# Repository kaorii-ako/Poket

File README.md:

# Poket

A pocket Bluetooth MP3 player built around an ESP32-S3.

Plays MP3s off a microSD card and sends them either to Bluetooth
headphones (A2DP source) or out a 3.5 mm jack.

> **Rev B changed the MCU.** The board started on an ESP32-S3, which turned out
> to have Bluetooth LE only — no BR/EDR — so A2DP could never have worked on it.
> `soc_caps.h` in ESP-IDF spells it out: the S3 defines `SOC_BLE_SUPPORTED` and
> not `SOC_BT_CLASSIC_SUPPORTED`. The classic ESP32 in the WROOM-32E-R2 has
> both, keeps its 2 MB PSRAM inside the chip package (so GPIO16/17 stay free,
> unlike a WROVER), and costs a USB-UART bridge because it has no native USB. 0.96" OLED, rotary
encoder, three transport buttons, LiPo with USB-C charging and a
coulomb-counting fuel gauge.

| | |
|---|---|
| MCU | ESP32-WROOM-32E-N16R2 (16 MB flash, 2 MB in-package PSRAM) |
| Storage | microSD over SPI |
| DAC | PCM5102A (I2S, internal PLL — no MCLK needed) |
| Headphone amp | PAM8908, charge-pump / ground-centred output |
| Charger | MCP73831, 500 mA, P-FET load share |
| Fuel gauge | BQ27441-G1 with 10 mΩ sense resistor |
| Rail | AP2112K-3.3, separate ferrite-isolated 3V3A for the audio |
| USB | CP2102N-A02 bridge + cross-coupled auto-reset (this part has no native USB) |
| Board | 80 × 54 mm, 4 layer (Sig / solid GND / Sig / Sig) |
| Case | 86 × 60 × 16.8 mm, 3D printed, two shells + slider cap, chamfered edges |

## The board

Top side: ESP32-S3 module and its antenna keepout top-right, audio chain and
power block under where the OLED sits, encoder centre-right, three transport
buttons along the bottom, USB-C bottom-right, 3.5 mm jack top-left.

Bottom side carries the microSD socket and the BOOT/RESET buttons, so the top
face stays clean. Right: all four copper layers together — In1.Cu is a solid
ground plane with no signal on it at all.

Full schematic (also as a PDF: [`docs/poket-schematic.pdf`](docs/poket-schematic.pdf)).
ERC clean — 0 errors, 0 warnings.

## The firmware

ESP-IDF v5.3, C. Reads MP3s off the card with a vendored [minimp3], decodes
into PSRAM and pushes PCM to either sink — I2S to the PCM5102A, or A2DP source
to a paired pair of headphones.

Six themes ship, and they are not palette swaps — a 1-bit 128 x 64 panel has no
colour to vary, so each one earns its difference through layout, typeface,
iconography and motion. Clockwise from top-left: **Minimal**, **Anime**
(a face that blinks on its own timer), **Cassette** (reels that wind across as
the track plays), **Y2K Chrome**, **Brutalist**, **Terminal**. A seventh slot
takes a custom theme uploaded from the browser; that one is *data*, not code,
so an uploaded pack can lay out screens but can never execute on the device.

The two smallest faces are a hand-drawn 5x8 bitmap table
([`tools/font5x8.py`](firmware/tools/font5x8.py)) — rasterising an outline at
7-8 px loses whole stems, and a 1-bit panel has no antialiasing to hide that
with. The rest come from real faces through
[`tools/mkfont.py`](firmware/tools/mkfont.py).

### Build and flash

ESP-IDF v5.3, target `esp32`. Full detail in
[`firmware/README.md`](firmware/README.md).

```bash
. $HOME/esp/esp-idf/export.sh
cd firmware
idf.py set-target esp32          # once
idf.py build
idf.py -p /dev/ttyUSB0 flash monitor
```

`sdkconfig.defaults` carries the flash size, PSRAM, Classic Bluetooth and the
partition table, so a clean tree builds without menuconfig. The CP2102N bridge
handles reset and boot mode, so flashing needs no button presses; if auto-reset
ever fails, hold **BOOT**, tap **RESET**, release **BOOT**.

Then: put MP3s in `/Music` on a FAT32 card, power on, long-press the encoder,
join the `Poket-XXXX` network shown on screen and open **http://192.168.4.1**.

### The web app

Hold the encoder and Poket brings up its own Wi-Fi access point and serves a
page: drag MP3s onto it to write them to the card, browse the library, drive
transport, and pick the screen theme with a **live 128 x 64 preview**. The
preview is not an artist's impression — `web/proto/oled.js` is a port of
`ui/gfx.c` and runs the same theme code against the same generated glyph bytes,
painted at an integer zoom so one panel pixel is exactly N x N screen pixels
with smoothing off.

Four design directions are prototyped in
[`firmware/web/proto/`](firmware/web/proto/) — open `index.html`:

| | |
|---|---|
| `jcard.html` | ink on cassette card stock; upload zone is a blank Side B |
| `bench.html` | desk instrument — keycaps with travel, knurled knob, amber readout |
| `fab.html` | the board documenting itself: silkscreen on solder mask, designators, title block |
| `plain.html` | the canon settings page; the control the other three have to beat |

Wi-Fi and Bluetooth share one radio, so while the page is being served audio
routes out the 3.5 mm jack.

[minimp3]: firmware/components/minimp3/

## Video

| | |
|---|---|
| [`video/poket-promo.mp4`](video/poket-promo.mp4) | 22 s product film — five shots, titles |
| [`video/poket-assembly.mp4`](video/poket-assembly.mp4) | 6.5 s — parts drop in, then a turntable |

Both are rendered from the same Blender scene, which rebuilds from scratch
with `blender/build_scene.py` (set `MODE` to `"promo"` or `"assembly"`).
Encode the PNG sequences with `tools/encode_video.sh`.

## Documentation

- [`docs/BOM.md`](docs/BOM.md) — bill of materials, ~$46/unit
- [`docs/ASSEMBLY.md`](docs/ASSEMBLY.md) — how to build one
- [`docs/DESIGN.md`](docs/DESIGN.md) — why each part was chosen, and the trade-offs
- [`docs/SUBMISSION.md`](docs/SUBMISSION.md) — what's done, what isn't
- [`JOURNAL.md`](JOURNAL.md) — build log

## Repo layout

```
poket.kicad_sch / .kicad_pcb / .kicad_pro   KiCad 10 project
firmware/                                   ESP-IDF app - drivers, audio, UI themes, web app
cad/enclosure.py                            parametric enclosure (FreeCAD, headless)
enclosure/*.step, *.stl                     exported case parts
docs/                                       BOM, assembly, design notes, schematic PDF
fab/                                        gerbers, drill, pick-and-place
images/                                     renders and screenshots
blender/                                    animation scene + board textures
video/                                      promo + assembly animations
tools/                                      fab export, video encode, PCB helper scripts
JOURNAL.md                                  build log
```

## Building the enclosure model

```
flatpak run --filesystem=host --command=FreeCADCmd org.freecad.FreeCAD cad/enclosure.py
```

Everything is driven by the constants at the top of `cad/enclosure.py`, so
if the PCB outline or a connector moves, change the number and re-run.

## Print settings

PETG or PLA, 0.2 mm layers, 4 perimeters, 20 % infill, no supports needed.
Front shell prints face-down, back shell prints tray-up. 4 × M2 heat-set
inserts (3.2 mm OD) in the front shell bosses; 4 × M2 × 12 screws from the
back.

## Status

**Hardware** — ERC **0 errors, 0 warnings**; DRC **0 errors, 0 schematic-parity
issues**, every signal net routed. The enclosure booleans against the real board
STEP with **0.0000 mm³** interference. Gerbers, drill and pick-and-place in
`fab/` are generated from this revision.

**Firmware** — complete and building. ESP-IDF v5.3, `idf.py build` succeeds from
a clean tree; `poket.bin` is 1.5 MB with 64 % of the app partition free. Drivers,
the audio path with A2DP linking, microSD over SPI, the library scanner, `.m3u`
playlists, the 1-bit graphics layer with six themes, the Wi-Fi access point, the
HTTP server and the web app are all in `firmware/`. Build and flash instructions:
[`firmware/README.md`](firmware/README.md).

**Not built.** No board has been fabricated, no part soldered, and no firmware
has ever run on hardware. Every image here is a render. The design is verified
in software and the firmware compiles — but "passes DRC and builds" and "works"
are different claims, and only the first is being made. Full gap list:
[`docs/SUBMISSION.md`](docs/SUBMISSION.md).

Three ground-pour fragments are untied, two of which carry a bypass capacitor's
ground. Documented rather than hidden.

## Design review

> **Not yet reviewed by another person.** This needs a second pair of eyes
> before fabrication, and nobody has given it one yet.
>
> When someone does, record it here: who reviewed it, when, what they flagged,
> and what changed as a result. An unreviewed board is a board with exactly one
> person's blind spots in it — and this project has already had one part choice
> that a reviewer would very likely have caught (the ESP32-S3 cannot do A2DP,
> which is the whole point of the device).

Worth a reviewer's attention in particular:

- **Power** — the MCP73831 charger, the DMG2301L load-share P-FET and the
  AP2112K rail, especially behaviour when USB and battery are both present.
- **The CP2102N block** — the 22.1 k/47.5 k VBUS sense divider and the
  cross-coupled auto-reset pair (`Q2` drives EN, `Q3` drives IO0, emitters
  cross). Both came from datasheets rather than from a copied schematic.
- **Strapping pins** — GPIO0, 2, 12 and 15. GPIO12 is deliberately left
  unconnected and the microSD runs on SPI to keep off it.
- **The antenna keepout** and whether the module is close enough to the board
  edge to radiate properly.

## License

MIT for code, CERN-OHL-S v2 for the hardware design files. See [`LICENSE`](LICENSE).

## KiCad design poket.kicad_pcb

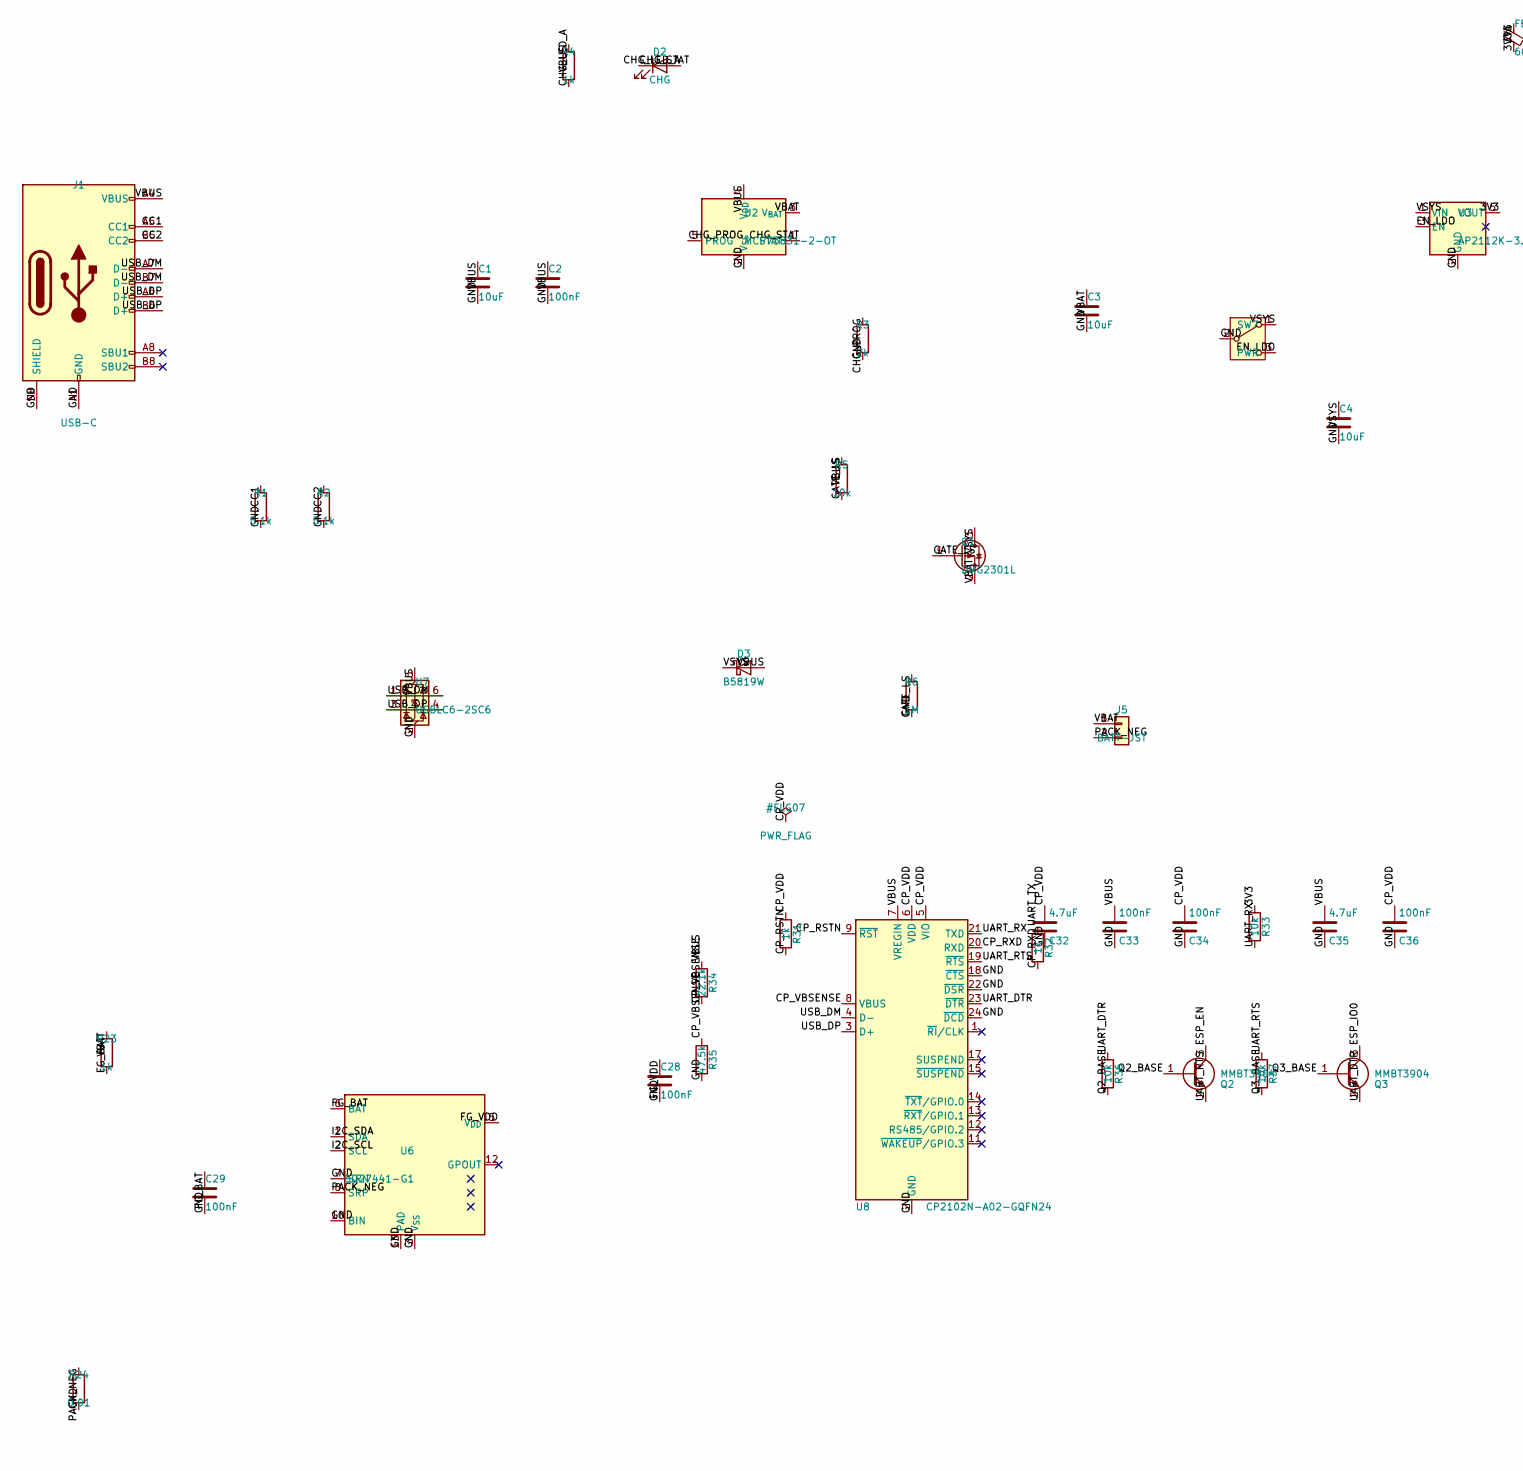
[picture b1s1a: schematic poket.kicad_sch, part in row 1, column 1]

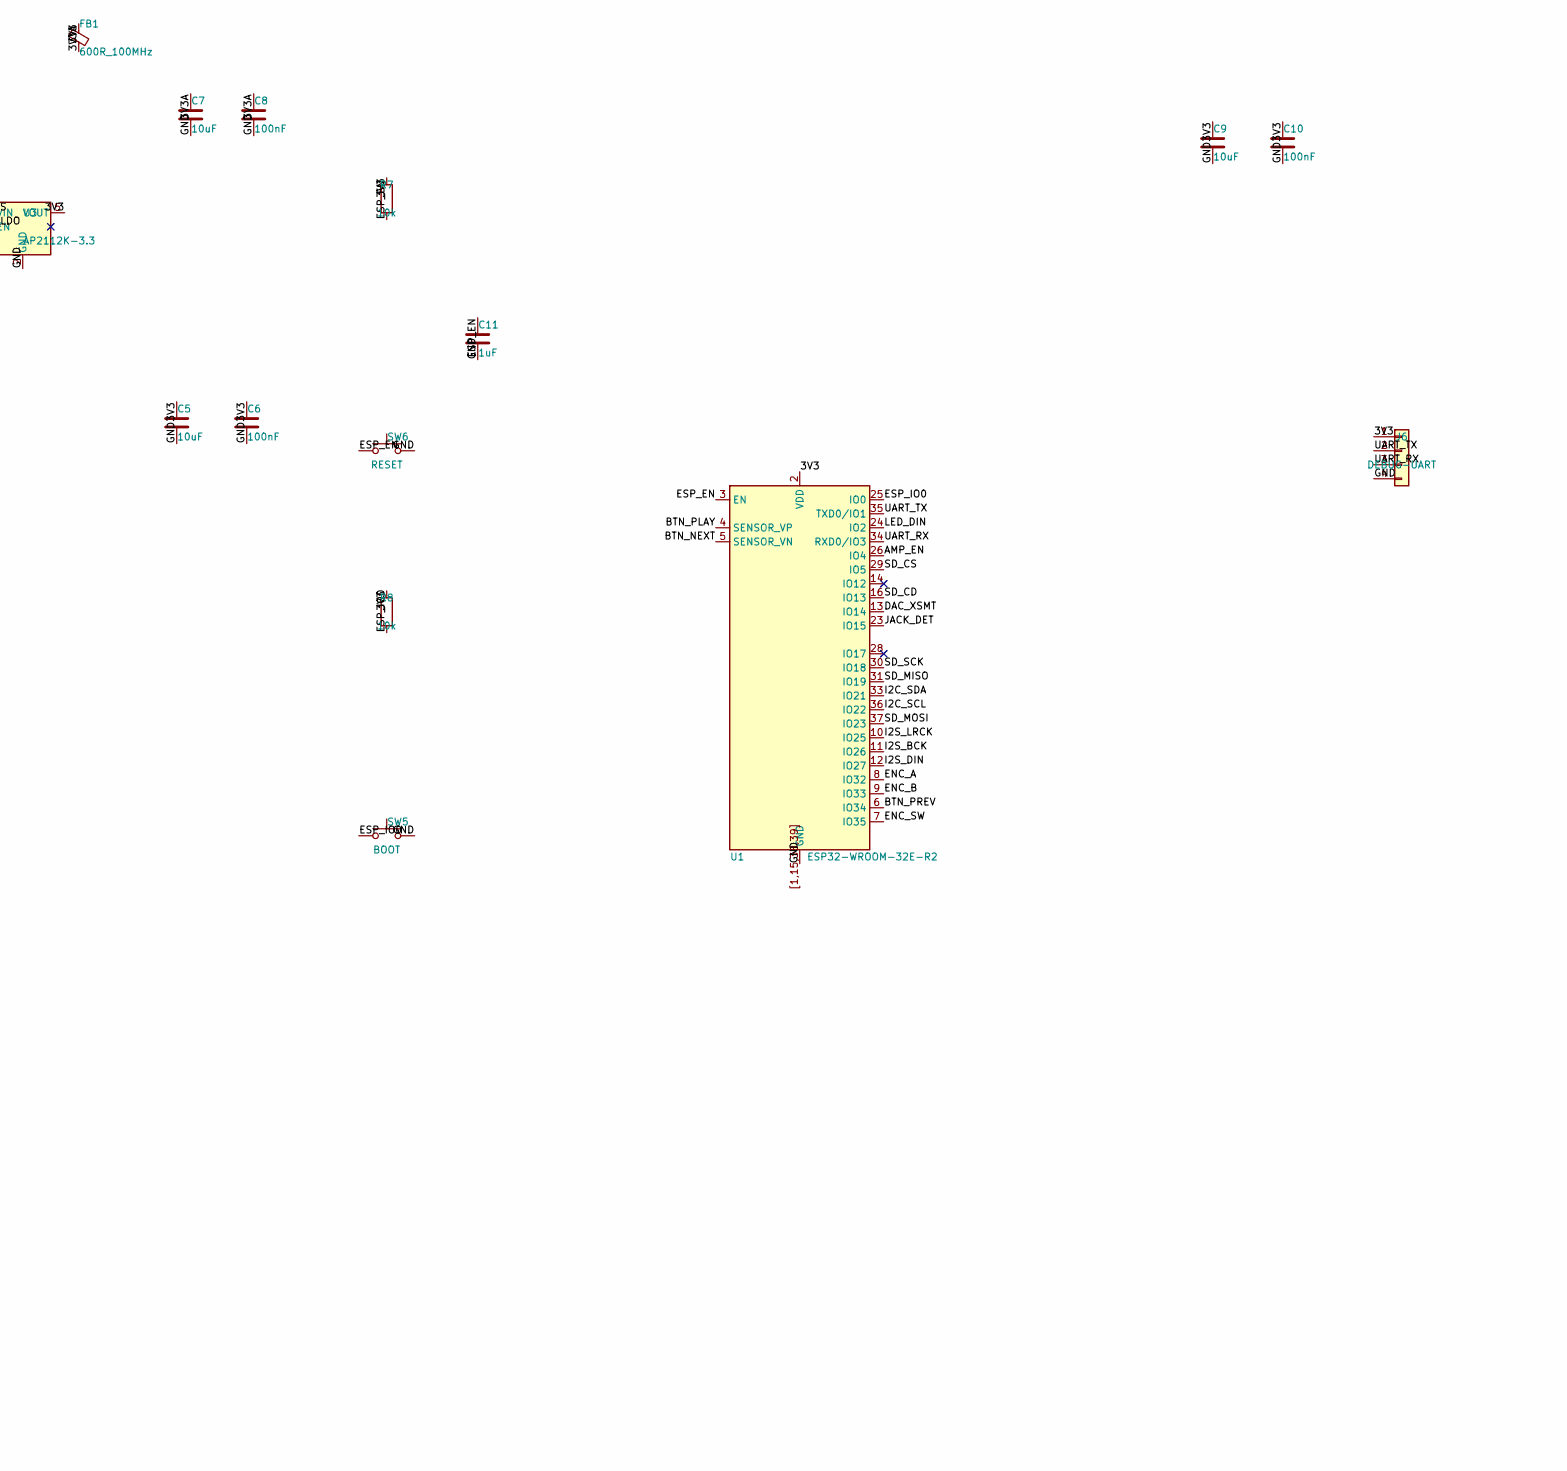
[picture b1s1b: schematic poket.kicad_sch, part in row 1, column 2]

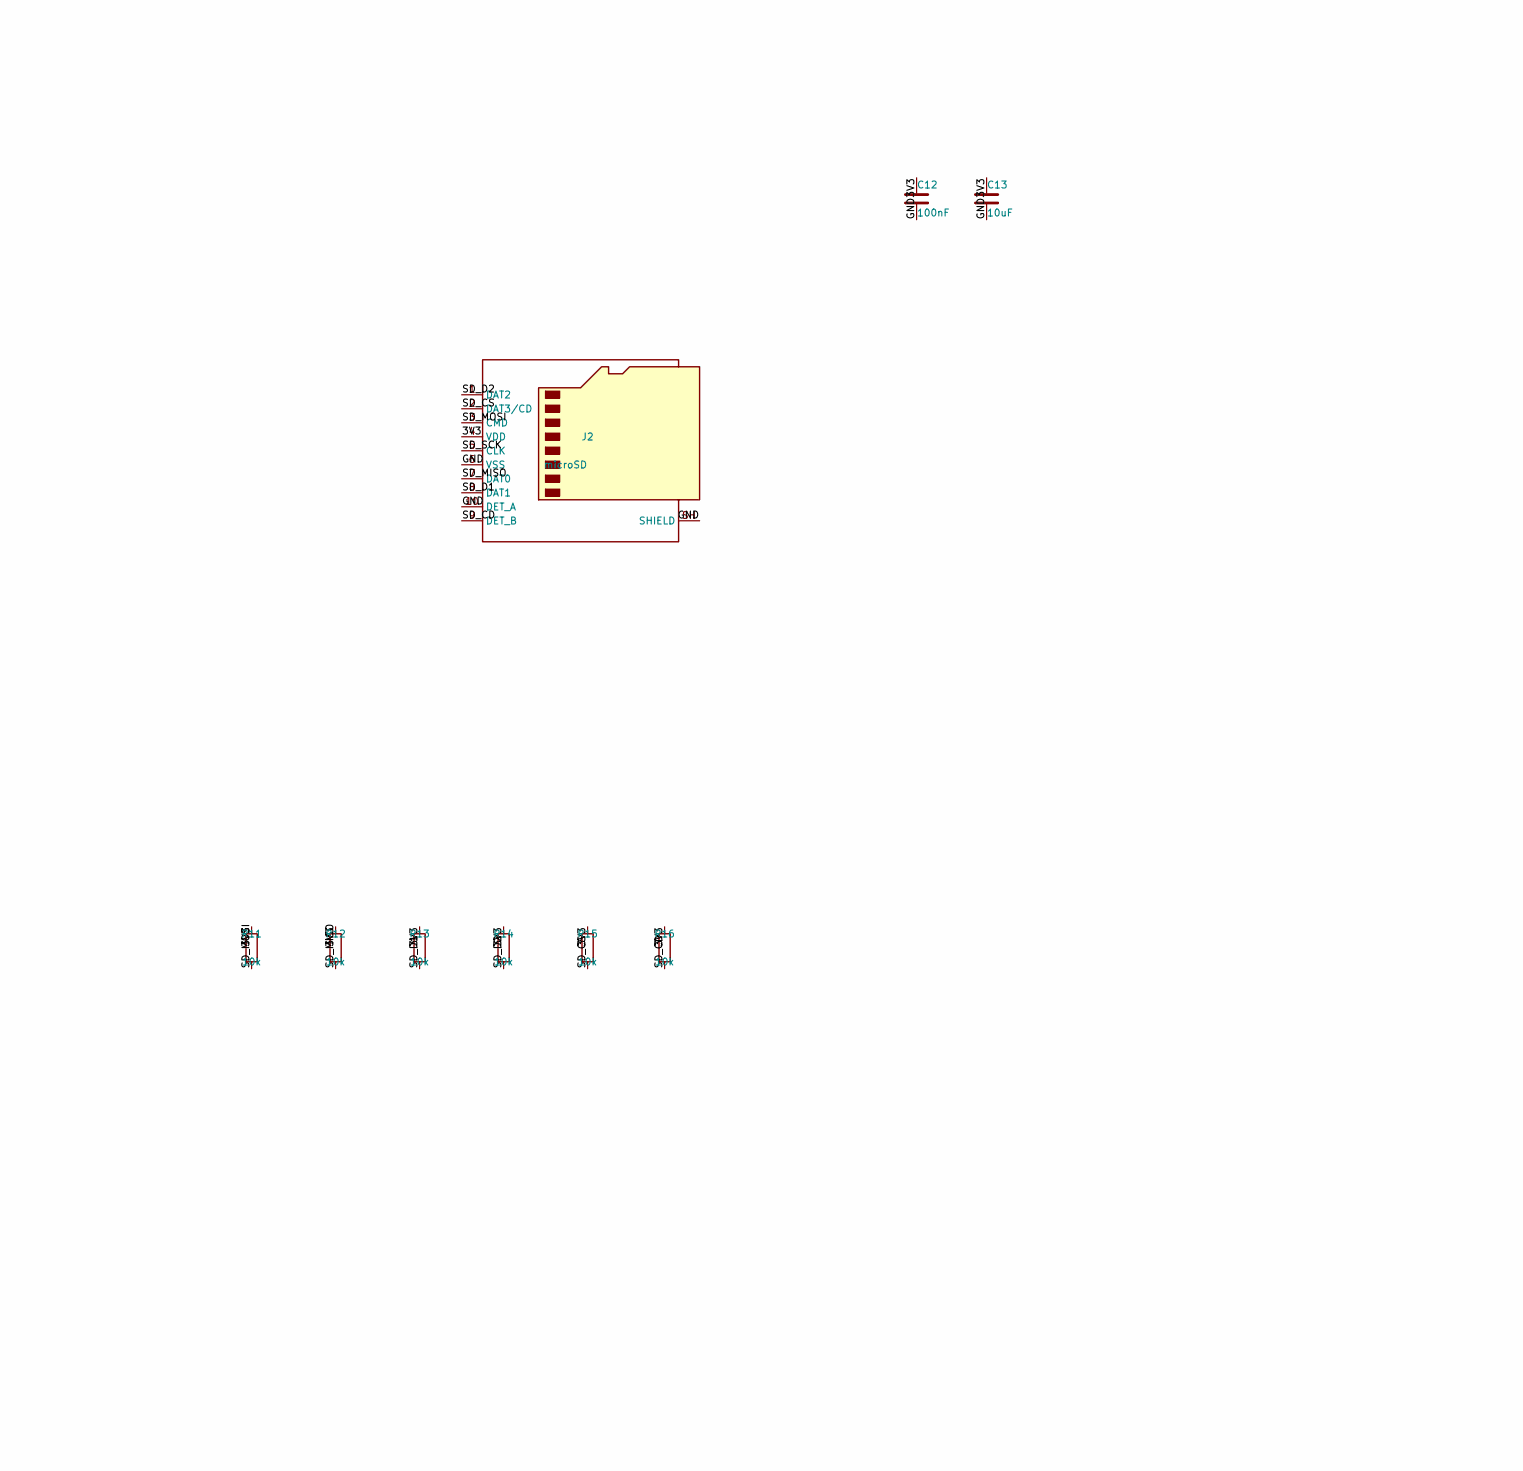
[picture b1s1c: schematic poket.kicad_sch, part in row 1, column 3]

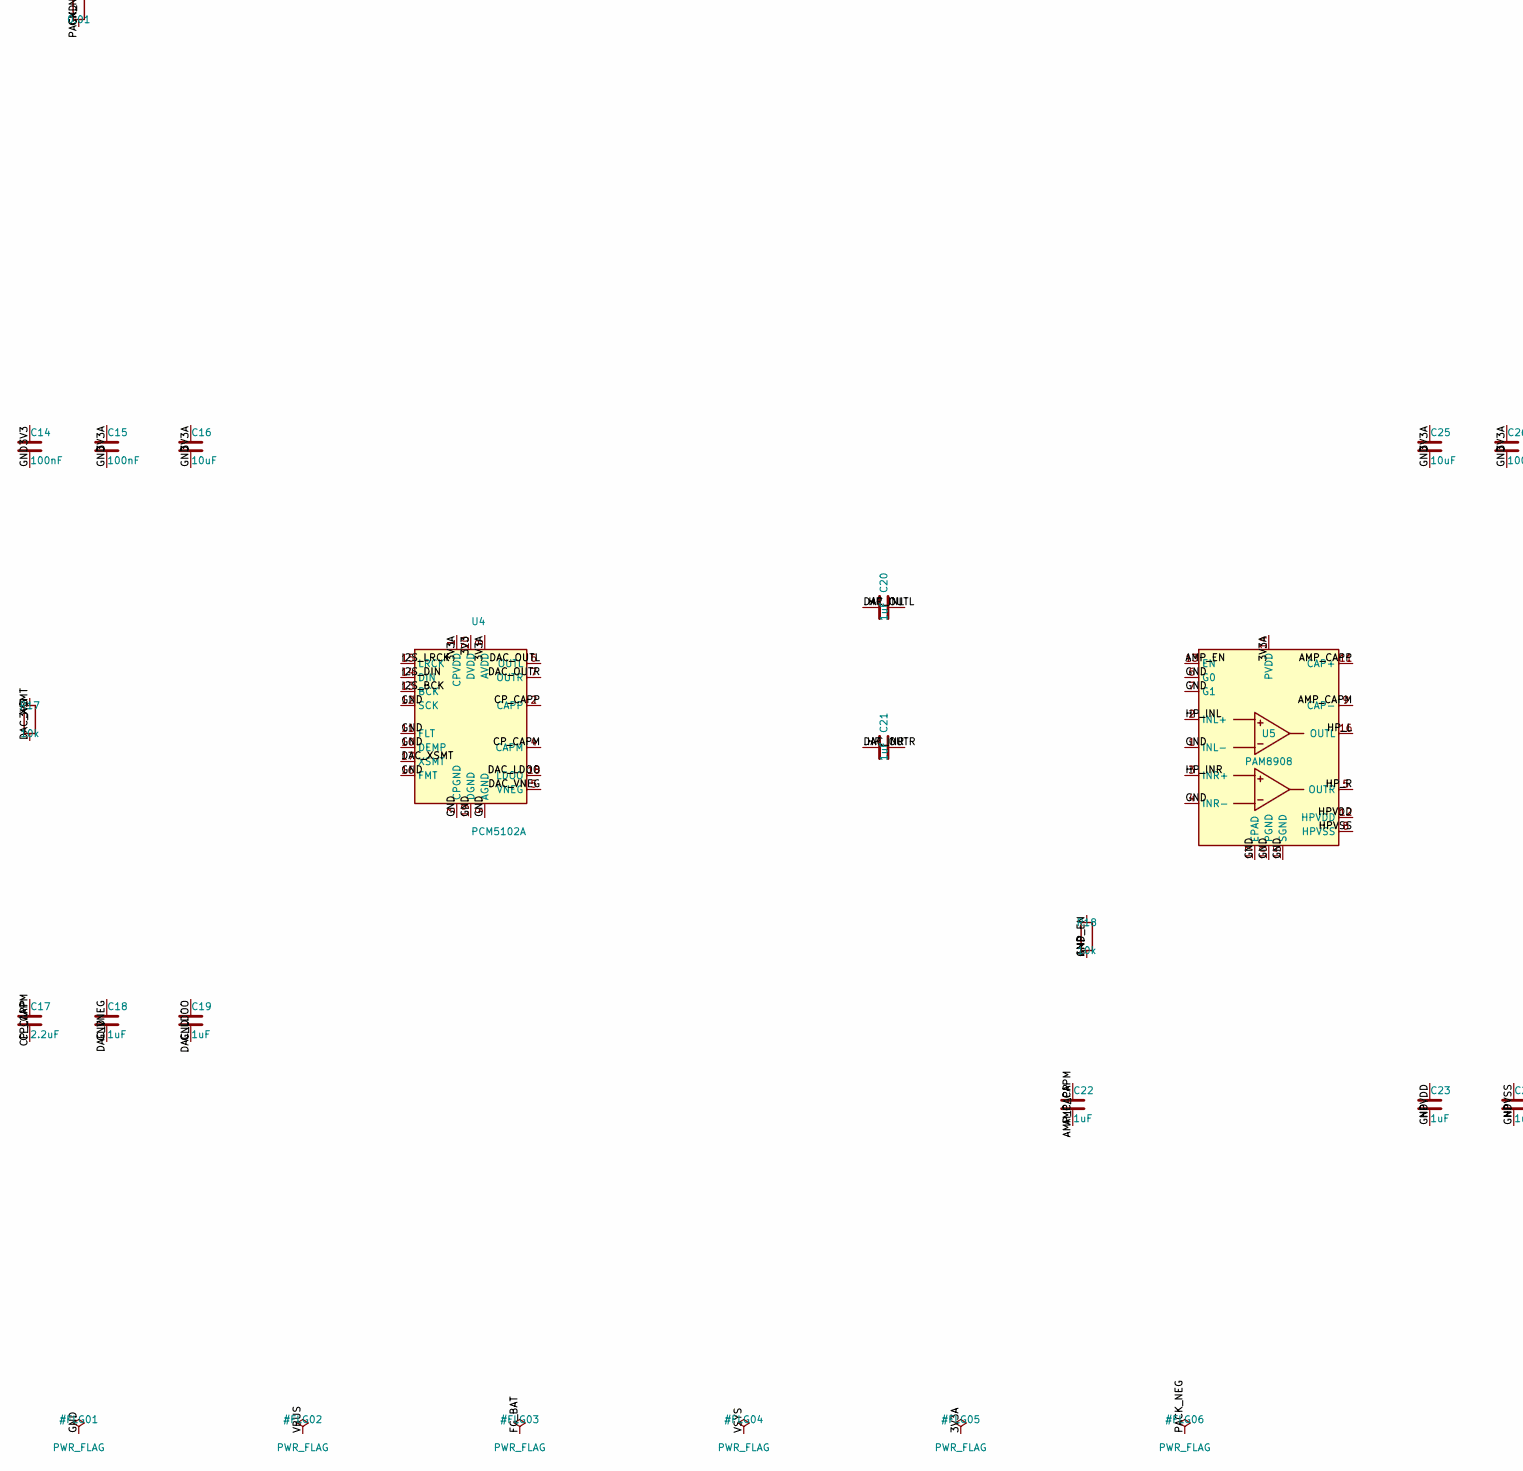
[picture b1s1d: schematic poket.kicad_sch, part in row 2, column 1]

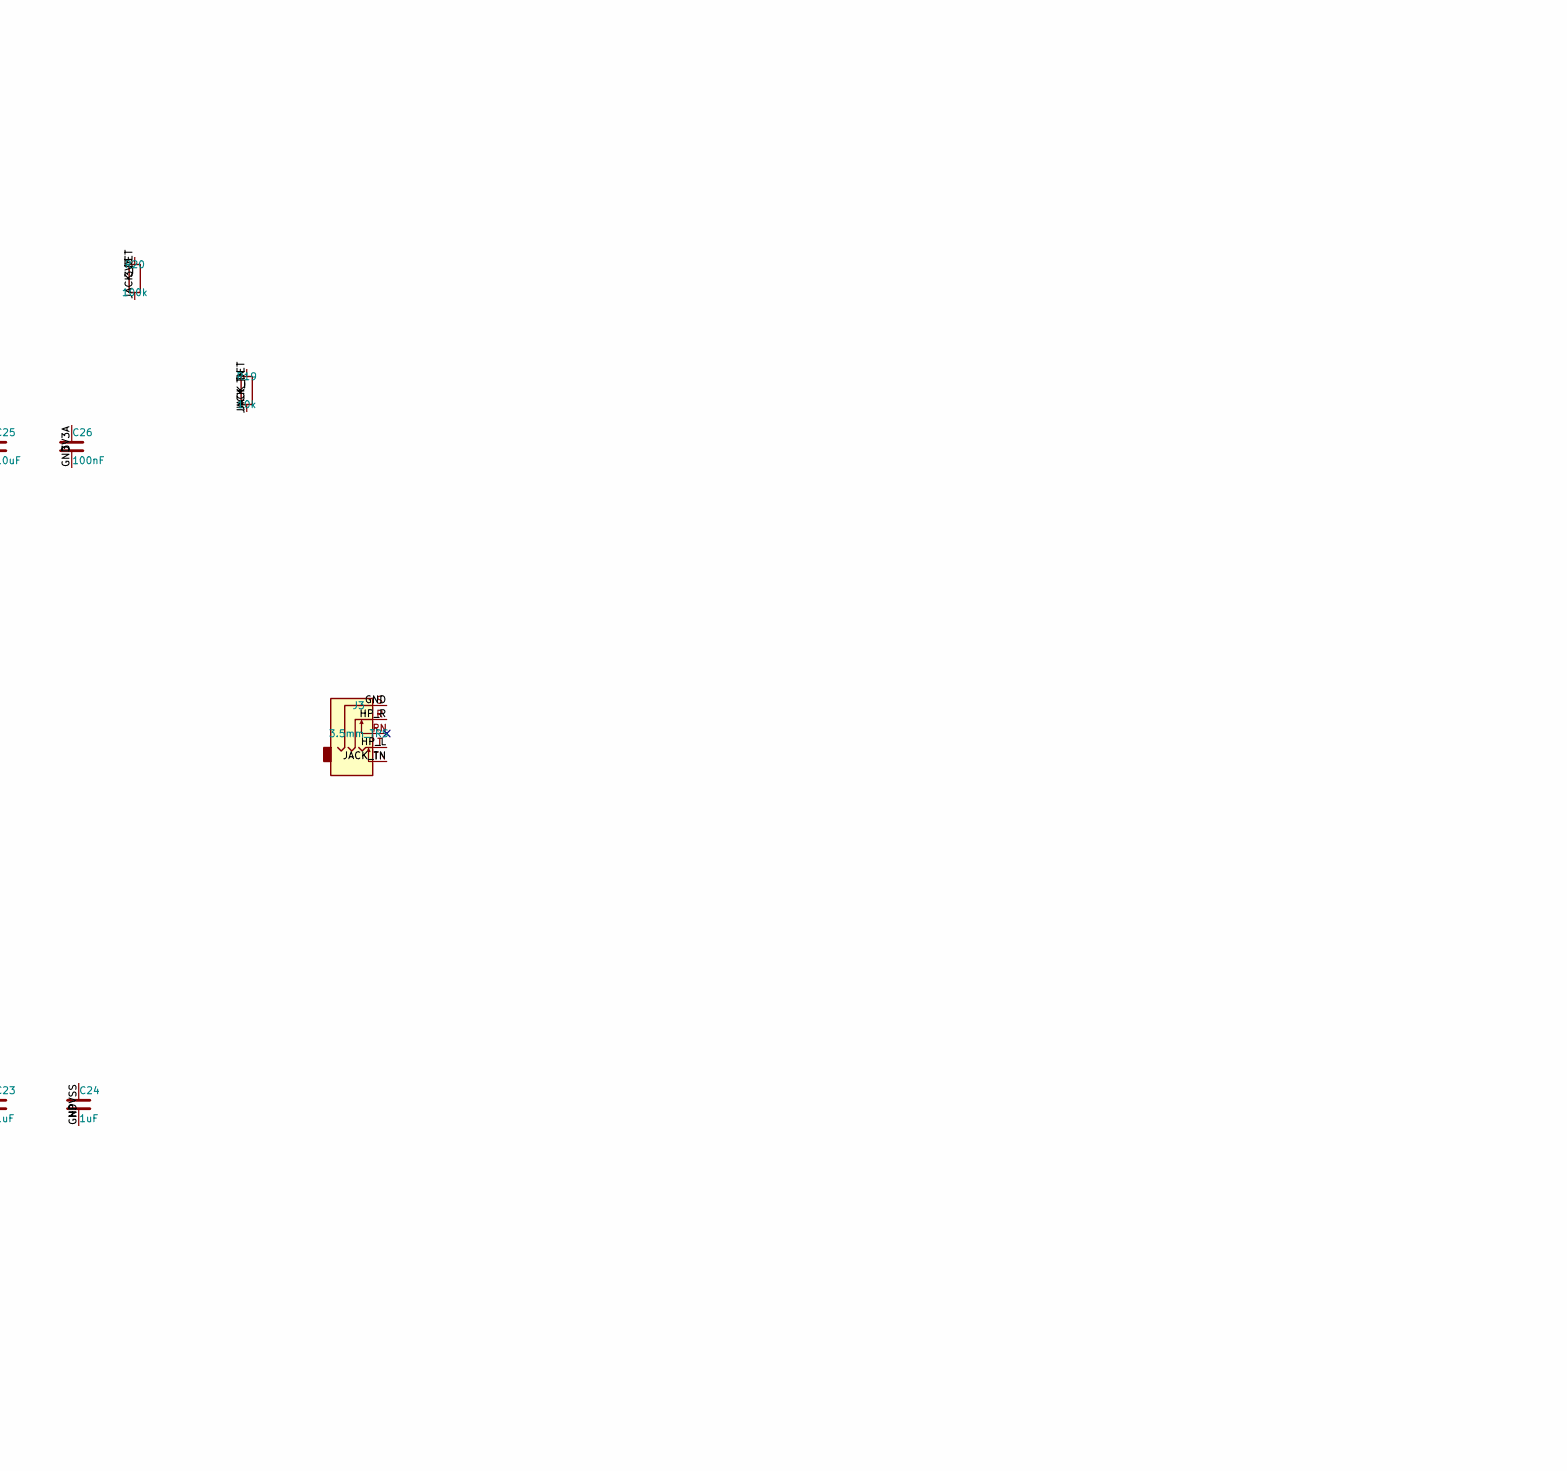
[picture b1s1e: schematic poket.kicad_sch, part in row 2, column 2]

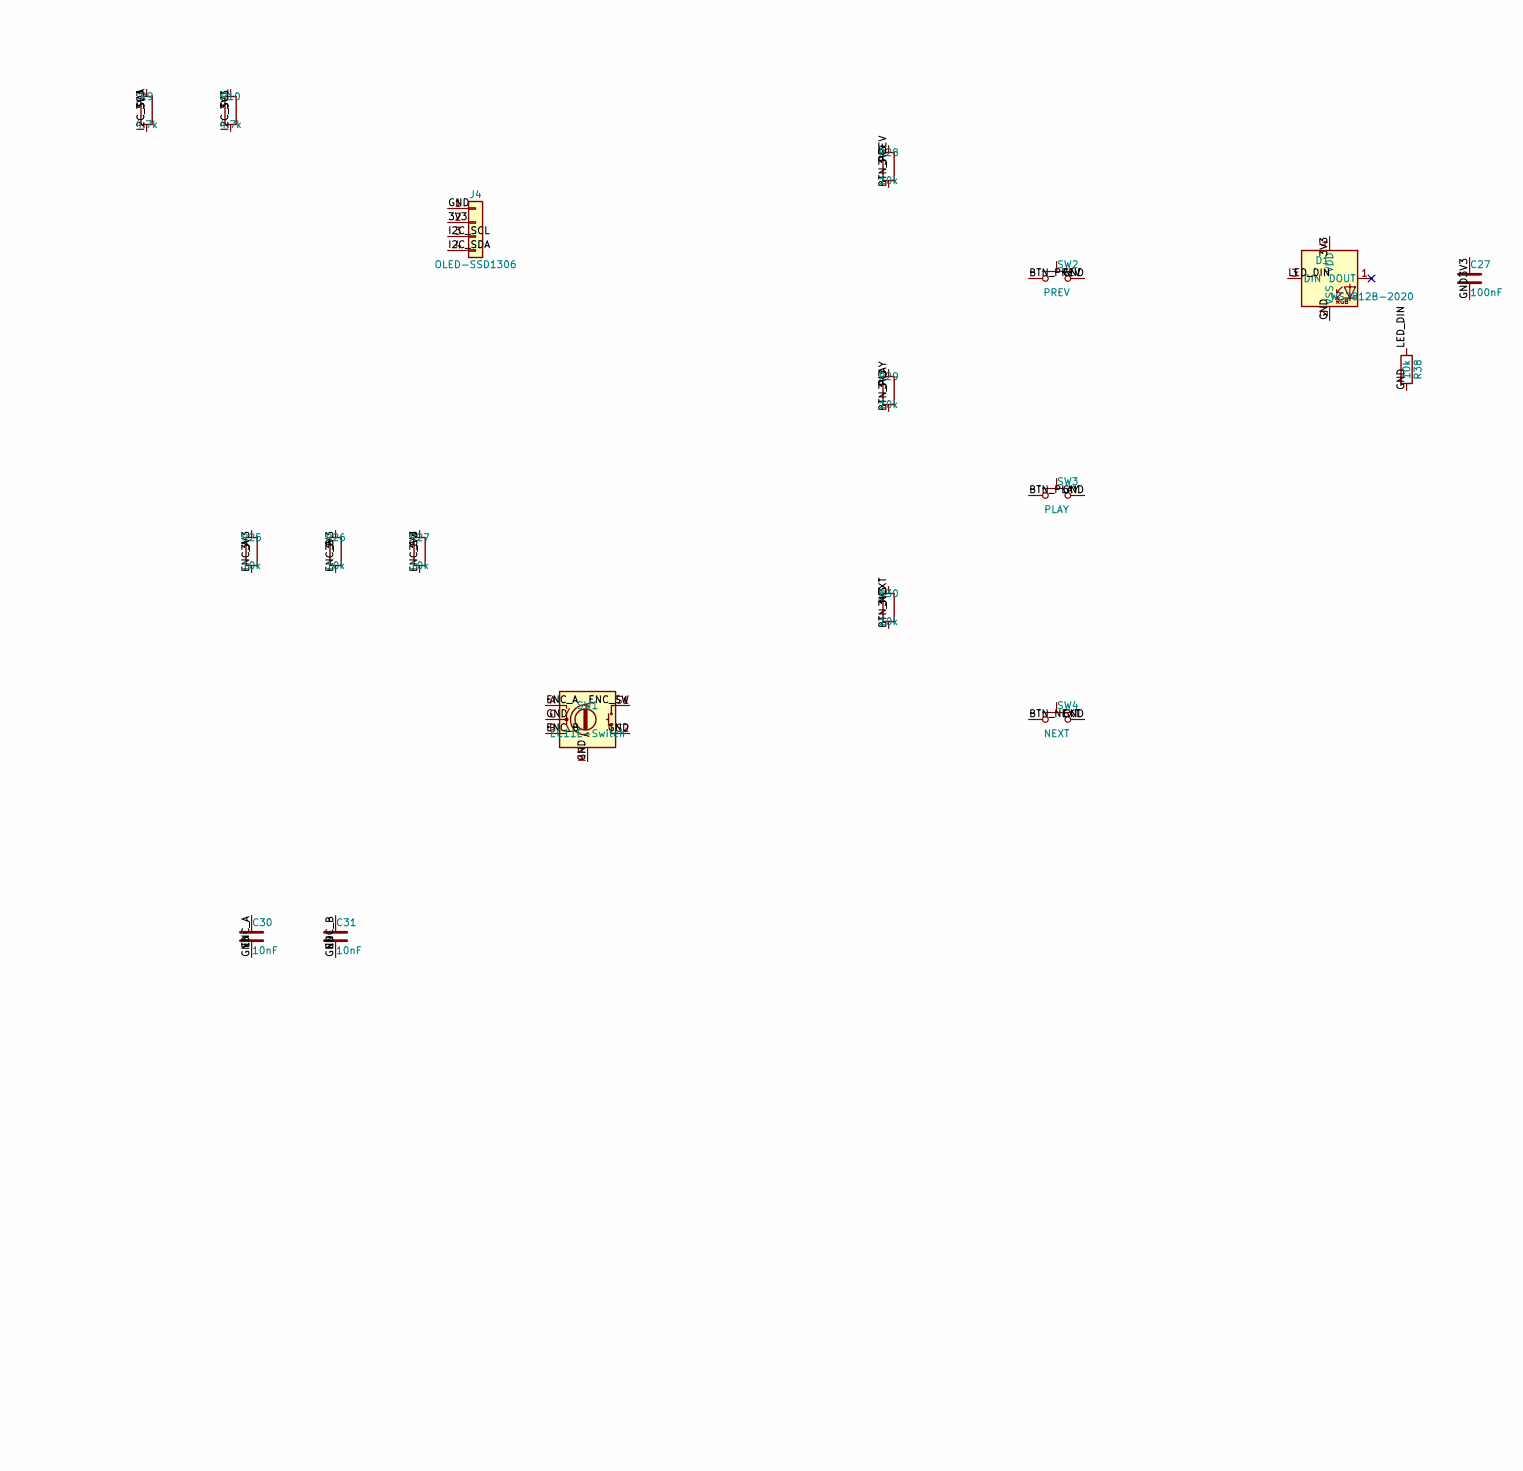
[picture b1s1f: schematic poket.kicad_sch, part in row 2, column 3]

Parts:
C1, C3, C4, C5, C7, C9, C13, C16, C25: 10uF; C_0805_2012Metric
C2, C6, C8, C10, C12, C14, C15, C26, C27, C28, C29, C33, C34, C36: 100nF; C_0603_1608Metric
C11, C18, C19, C20, C21, C22, C23, C24: 1uF; C_0603_1608Metric
C17: 2.2uF; C_0603_1608Metric
C30, C31: 10nF; C_0603_1608Metric
C32, C35: 4.7uF; C_0603_1608Metric
D1: WS2812B-2020; LED_WS2812B-2020_PLCC4_2.0x2.0mm
D2: CHG; LED_0603_1608Metric
D3: B5819W; D_SOD-123
FB1: 600R_100MHz; L_0603_1608Metric
J1: USB-C; USB_C_Receptacle_HCTL_HC-TYPE-C-16P-01A
J2: microSD; microSD_HC_Hirose_DM3AT-SF-PEJM5
J3: 3.5mm_TRS; Jack_3.5mm_CUI_SJ1-3535NG_Horizontal
J4: OLED-SSD1306; PinHeader_1x04_P2.54mm_Vertical
J5: BATT-JST; JST_PH_S2B-PH-SM4-TB_1x02-1MP_P2.00mm_Horizontal
J6: DEBUG-UART; PinHeader_1x04_P2.54mm_Vertical
Q1: DMG2301L; SOT-23
Q2, Q3: MMBT3904; SOT-23
R1, R2: 5.1k; R_0603_1608Metric
R3: 2k; R_0603_1608Metric
R4, R23, R31, R32: 1k; R_0603_1608Metric
R5, R7, R8, R11, R12, R13, R14, R15, R16, R17, R18, R19, R25, R26, R27, R28, R29, R30, R33, R36, R37, R38: 10k; R_0603_1608Metric
R6: 1M; R_0603_1608Metric
R9, R10: 4.7k; R_0603_1608Metric
R20: 100k; R_0603_1608Metric
R24: 0.01; R_1206_3216Metric
R34: 22.1k; R_0603_1608Metric
R35: 47.5k; R_0603_1608Metric
SW1: EC11E-Switch; RotaryEncoder_Alps_EC11E-Switch_Vertical_H20mm
SW2: PREV; SW_Push_1TS009xxxx-xxxx-xxxx_6x6x5mm
SW3: PLAY; SW_Push_1TS009xxxx-xxxx-xxxx_6x6x5mm
SW4: NEXT; SW_Push_1TS009xxxx-xxxx-xxxx_6x6x5mm
SW5: BOOT; SW_SPST_B3U-1000P
SW6: RESET; SW_SPST_B3U-1000P
SW7: PWR; SW_SPDT_PCM12
U1: ESP32-WROOM-32E-R2; ESP32-WROOM-32E
U2: MCP73831-2-OT; SOT-23-5
U3: AP2112K-3.3; SOT-23-5
U4: PCM5102A; TSSOP-20_4.4x6.5mm_P0.65mm
U5: PAM8908; QFN-16-1EP_3x3mm_P0.5mm_EP1.7x1.7mm
U6: BQ27441-G1; Texas_S-PDSO-N12
U7: USBLC6-2SC6; SOT-23-6
U8: CP2102N-A02-GQFN24; QFN-24-1EP_4x4mm_P0.5mm_EP2.6x2.6mm

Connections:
3V3: C5.1, C6.1, C9.1, C10.1, C12.1, C13.1, C14.1, C27.1, D1.4 (VDD), FB1.1, J2.4 (VDD), J4.2, J6.1, R7.1, R8.1, R9.1, R10.1, R11.1, R12.1, R13.1, R14.1, R15.1, R16.1, R17.1, R20.1, R25.1, R26.1, R27.1, R28.1, R29.1, R30.1, R33.1, U1.2 (VDD), U3.5 (VOUT), U4.20 (DVDD)
3V3A: C7.1, C8.1, C15.1, C16.1, C25.1, C26.1, FB1.2, U4.1 (CPVDD), U4.8 (AVDD), U5.14 (PVDD)
AMP_CAPM: C22.2, U5.9 (CAP-)
AMP_CAPP: C22.1, U5.11 (CAP+)
AMP_EN: R18.1, U1.26 (IO4), U5.13 (EN)
BTN_NEXT: R30.2, SW4.1, U1.5 (SENSOR_VN)
BTN_PLAY: R29.2, SW3.1, U1.4 (SENSOR_VP)
BTN_PREV: R28.2, SW2.1, U1.6 (IO34)
CC1: J1.A5 (CC1), R1.1
CC2: J1.B5 (CC2), R2.1
CHG_LED_A: D2.2 (A), R4.2
CHG_PROG: R3.1, U2.5 (PROG)
CHG_STAT: D2.1 (K), U2.1 (STAT)
CP_CAPM: C17.2, U4.4 (CAPM)
CP_CAPP: C17.1, U4.2 (CAPP)
CP_RSTN: R31.2, U8.9 (~RST)
CP_RXD: R32.2, U8.20 (RXD)
CP_VBSENSE: R34.2, R35.1, U8.8 (VBUS)
CP_VDD: C32.1, C34.1, C36.1, R31.1, U8.5 (VIO), U8.6 (VDD)
DAC_LDOO: C19.1, U4.18 (LDOO)
DAC_OUTL: C20.1, U4.6 (OUTL)
DAC_OUTR: C21.1, U4.7 (OUTR)
DAC_VNEG: C18.1, U4.5 (VNEG)
DAC_XSMT: R17.2, U1.13 (IO14), U4.17 (XSMT)
ENC_A: C30.1, R25.2, SW1.A, U1.8 (IO32)
ENC_B: C31.1, R26.2, SW1.B, U1.9 (IO33)
ENC_SW: R27.2, SW1.S1, U1.7 (IO35)
EN_LDO: SW7.3 (C), U3.3 (EN)
ESP_EN: C11.1, Q2.3 (C), R7.2, SW6.1, U1.3 (EN)
ESP_IO0: Q3.3 (C), R8.2, SW5.1, U1.25 (IO0)
FG_BAT: C29.1, R23.2, U6.6 (BAT)
FG_GPOUT: U6.12 (GPOUT)
FG_VDD: C28.1, U6.5 (V_{DD})
GATE_LS: Q1.1 (G), R5.2, R6.1
GND: C1.2, C2.2, C3.2, C4.2, C5.2, C6.2, C7.2, C8.2, C9.2, C10.2, C11.2, C12.2, C13.2, C14.2, C15.2, C16.2, C18.2, C19.2, C23.2, C24.2, C25.2, C26.2, C27.2, C28.2, C29.2, C30.2, C31.2, C32.2, C33.2, C34.2, C35.2, C36.2, D1.2 (VSS), J1.A1 (GND), J1.A12 (GND), J1.B1 (GND), J1.B12 (GND), J1.SH (SHIELD), J2.6 (VSS), J2.10 (DET_A), J2.SH (SHIELD), J3.S, J4.1, J6.4, R1.2, R2.2, R3.2, R6.2, R18.2, R24.2, R35.2, R38.2, SW1.C, SW1.MP, SW1.S2, SW2.2, SW3.2, SW4.2, SW5.2, SW6.2, SW7.2 (B), U1.1, U1.15, U1.38, U1.39, U1.[1,15,38,39] (GND), U2.2 (V_{SS}), U3.2 (GND), U4.3 (CPGND), U4.9 (AGND), U4.10 (DEMP), U4.11 (FLT), U4.12 (SCK), U4.16 (FMT), U4.19 (DGND), U5.1 (INL-), U5.4 (INR-), U5.6 (G0), U5.7 (G1), U5.10 (PGND), U5.15 (SGND), U5.17 (EPAD), U6.3 (V_{SS}), U6.7 (SRN), U6.10 (BIN), U6.13 (PAD), U7.2 (GND), U8.2 (GND), U8.18 (~CTS), U8.22 (~DSR), U8.24 (~DCD), U8.25 (GND)
HPVDD: C23.1, U5.12 (HPVDD)
HPVSS: C24.1, U5.8 (HPVSS)
HP_INL: C20.2, U5.2 (INL+)
HP_INR: C21.2, U5.3 (INR+)
HP_L: J3.T, U5.16 (OUTL)
HP_R: J3.R, U5.5 (OUTR)
I2C_SCL: J4.3, R10.2, U1.36 (IO22), U6.2 (SCL)
I2C_SDA: J4.4, R9.2, U1.33 (IO21), U6.1 (SDA)
I2S_BCK: U1.11 (IO26), U4.13 (BCK)
I2S_DIN: U1.12 (IO27), U4.14 (DIN)
I2S_LRCK: U1.10 (IO25), U4.15 (LRCK)
JACK_DET: R19.2, R20.2, U1.23 (IO15)
JACK_TN: J3.TN, R19.1
LED_DIN: D1.3 (DIN), R38.1, U1.24 (IO2)
PACK_NEG: J5.2, R24.1, U6.8 (SRP)
Q2_BASE: Q2.1 (B), R36.2
Q3_BASE: Q3.1 (B), R37.2
SD_CD: J2.9 (DET_B), R16.2, U1.16 (IO13)
SD_CS: J2.2 (DAT3/CD), R15.2, U1.29 (IO5)
SD_D1: J2.8 (DAT1), R13.2
SD_D2: J2.1 (DAT2), R14.2
SD_MISO: J2.7 (DAT0), R12.2, U1.31 (IO19)
SD_MOSI: J2.3 (CMD), R11.2, U1.37 (IO23)
SD_SCK: J2.5 (CLK), U1.30 (IO18)
UART_DTR: Q3.2 (E), R36.1, U8.23 (~DTR)
UART_RTS: Q2.2 (E), R37.1, U8.19 (~RTS)
UART_RX: J6.3, R33.2, U1.34 (RXD0/IO3), U8.21 (TXD)
UART_TX: J6.2, R32.1, U1.35 (TXD0/IO1)
USB_DM: J1.A7 (D-), J1.B7 (D-), U7.1 (I/O1), U7.6 (I/O1), U8.4 (D-)
USB_DP: J1.A6 (D+), J1.B6 (D+), U7.3 (I/O2), U7.4 (I/O2), U8.3 (D+)
VBAT: C3.1, J5.1, Q1.2 (S), R23.1, U2.3 (V_{BAT})
VBUS: C1.1, C2.1, C33.1, C35.1, D3.2 (A), J1.A4 (VBUS), J1.A9 (VBUS), J1.B4 (VBUS), J1.B9 (VBUS), R4.1, R5.1, R34.1, U2.4 (V_{DD}), U7.5 (VBUS), U8.7 (VREGIN)
VSYS: C4.1, D3.1 (K), Q1.3 (D), SW7.1 (A), U3.1 (VIN)
